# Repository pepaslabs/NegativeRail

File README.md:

# NegativeRail

An ICL7660-based negative rail daughter board.

# Development

See my eevblog.com [forum thread](https://www.eevblog.com/forum/projects/an-evening-with-the-icl7660/) for lots of oscilloscope screenshots as I tested various iterations of this design.

# Status

This board has been tested using the [dutch oven faraday cage](https://www.eevblog.com/forum/beginners/the-$20-desktop-faraday-cage/):

Performance matches that of the prototype (see the eevblog.com [forum thread](https://www.eevblog.com/forum/projects/an-evening-with-the-icl7660/)).

Noise into a 1k load:

Noise with power supply disconnected (i.e., noise floor of measurement system):

This indicates that the ~750kHz spikes are not coming from the ICL7660 board (perhaps this is due to the switch-mode power supply inside of the scope?).

# Board design v1

Initial board design.

## Gerbers

[gerbers.zip](releases/v1/gerbers.zip)

## Schematic

[PDF](releases/v1/ICL7660-schematic.pdf).

# License

This board design is [Open-Source Hardware](http://www.oshwa.org/definition/).  It is licensed under the [MIT License](http://opensource.org/licenses/MIT).  It was designed by Jason Pepas.

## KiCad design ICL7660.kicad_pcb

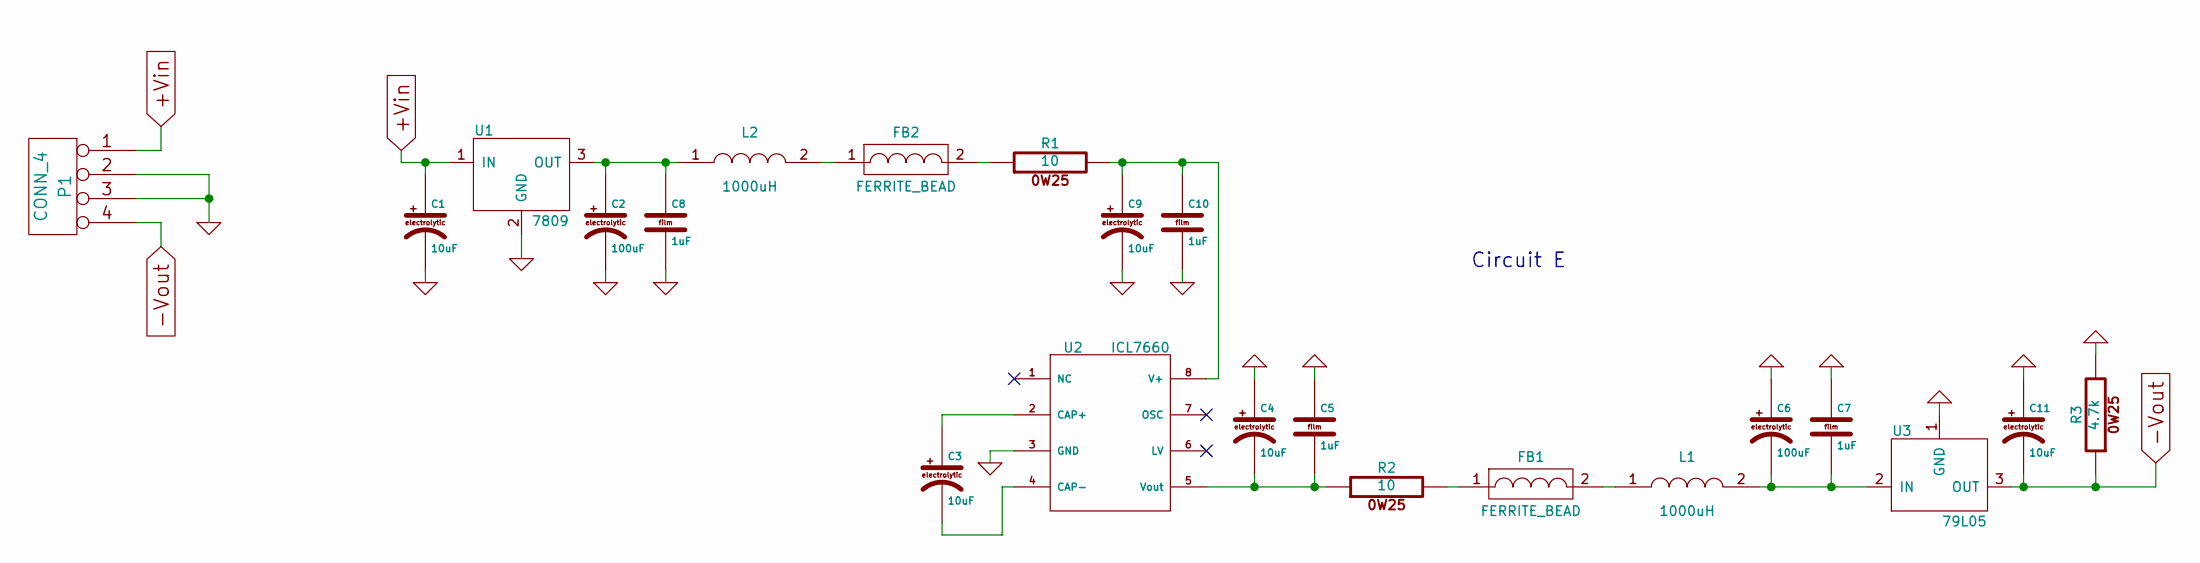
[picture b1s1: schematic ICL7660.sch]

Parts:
C1, C3, C4, C9, C11: 10uF
C2, C6: 100uF
C5, C7, C8, C10: 1uF
FB1, FB2: FERRITE_BEAD
L1, L2: 1000uH
P1: CONN_4
R1, R2: 10
R3: 4.7k
U1: 7809
U2: ICL7660
U3: 79L05

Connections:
+Vin: C1.1, P1.1, U1.1 (IN)
-Vout: C11.2, P1.4, R3.1, U3.3 (OUT)
GND: C1.2, C2.2, C4.1, C5.1, C6.1, C7.1, C8.2, C9.2, C10.2, C11.1, P1.2, P1.3, R3.2, U1.2 (GND), U2.3 (GND), U3.1 (GND)
unnamed: FB2.1, L2.2
unnamed: FB2.2, R1.1
unnamed: FB1.1, R2.2
unnamed: C2.1, C8.1, L2.1, U1.3 (OUT)
unnamed: C3.2, U2.4 (CAP-)
unnamed: C3.1, U2.2 (CAP+)
unnamed: C9.1, C10.1, R1.2, U2.8 (V+)
unnamed: C6.2, C7.2, L1.2, U3.2 (IN)
unnamed: FB1.2, L1.1
unnamed: C4.2, C5.2, R2.1, U2.5 (Vout)

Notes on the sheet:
Circuit E

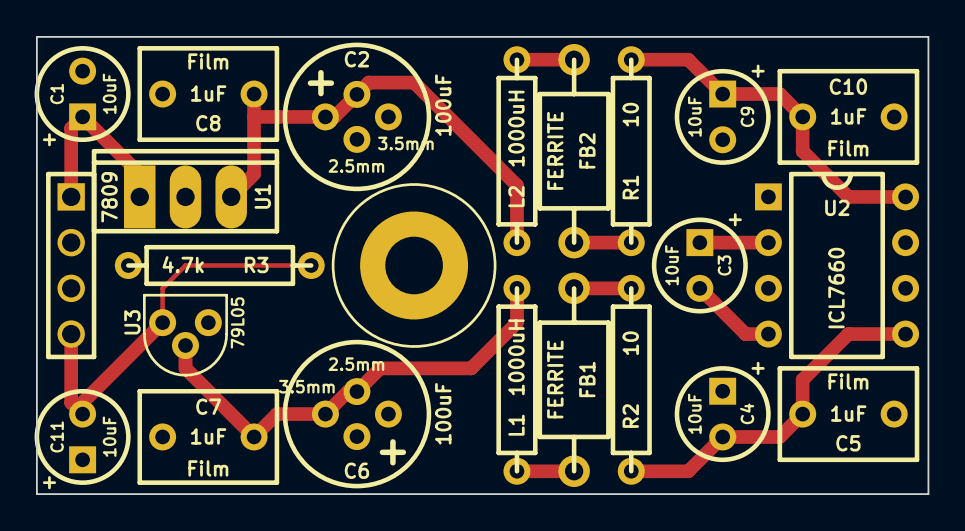
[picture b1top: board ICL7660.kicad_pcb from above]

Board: 2 copper layers, 49.5 x 25.4 mm, 23 parts (0 on the bottom side), 13 nets.

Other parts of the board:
H***: Val**; hole_M3

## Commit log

2014-08-03 initial implementation
2014-08-03 v1 gerbers
2014-08-03 adding OSHW logo to v1 gerbers.
2017-04-22 file organization
2017-04-22 adding schematic
2017-05-20 adding photos
2017-05-20 adding photos, scope screenshots
2017-05-20 fixing scope screenshot
2017-05-20 rotating schematic
